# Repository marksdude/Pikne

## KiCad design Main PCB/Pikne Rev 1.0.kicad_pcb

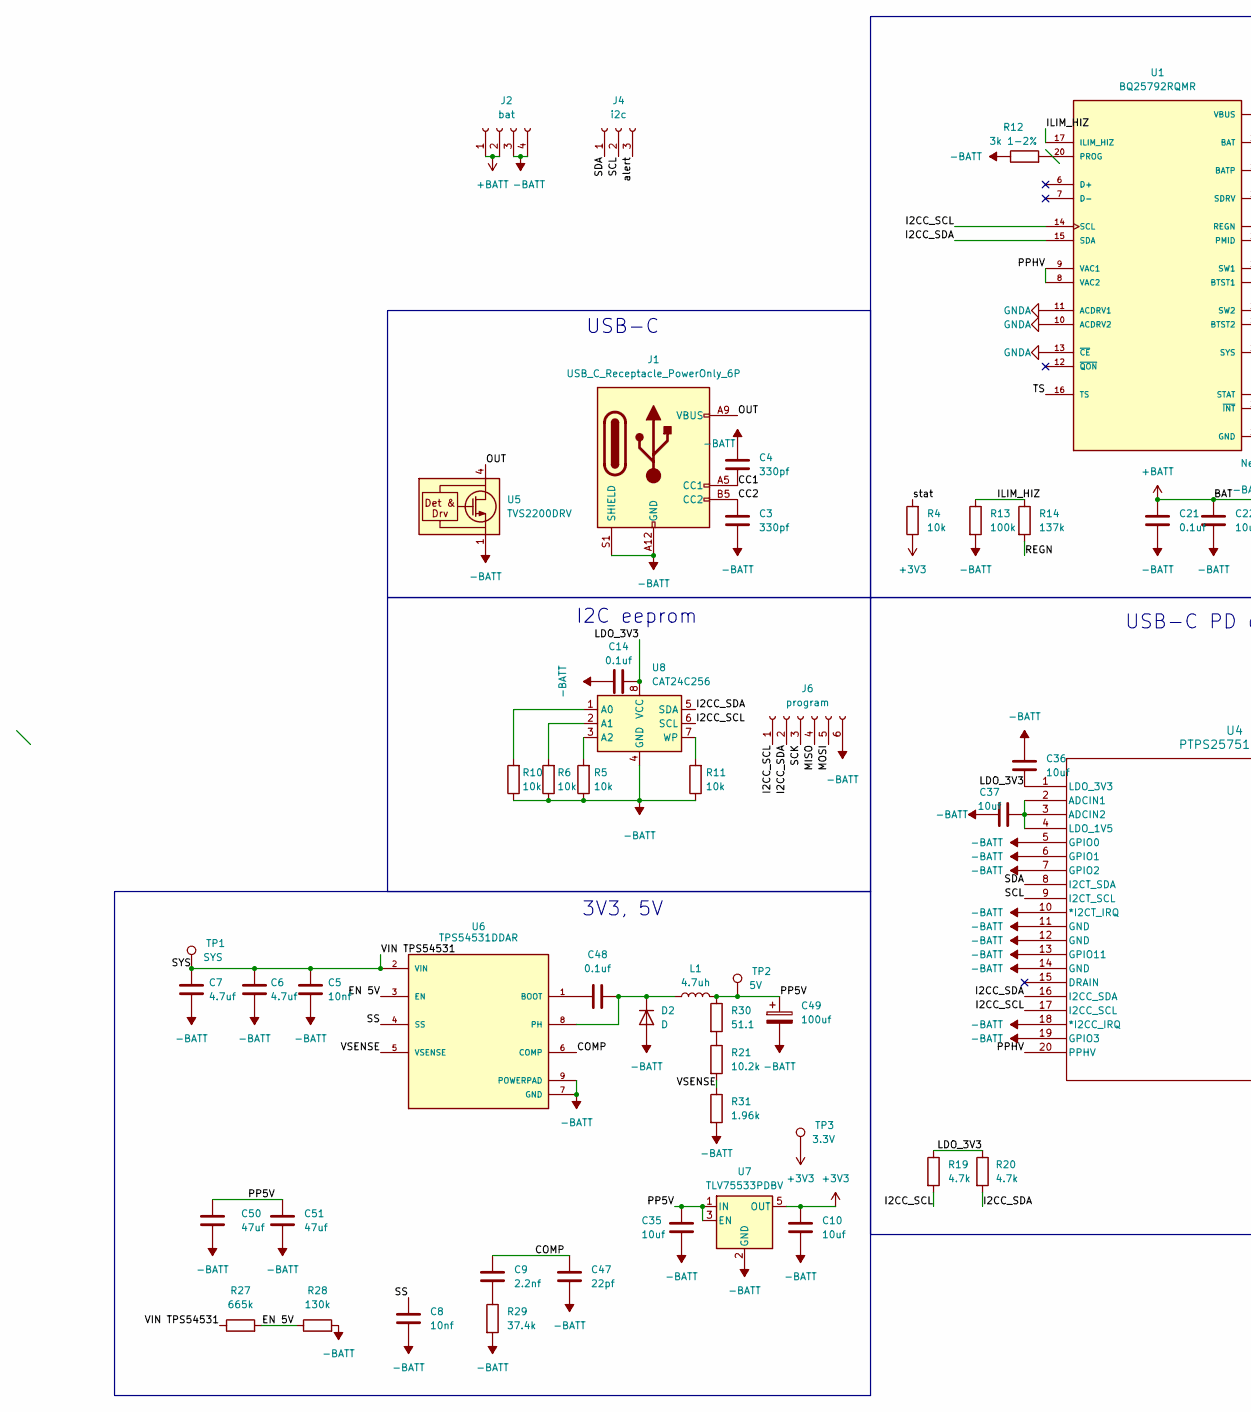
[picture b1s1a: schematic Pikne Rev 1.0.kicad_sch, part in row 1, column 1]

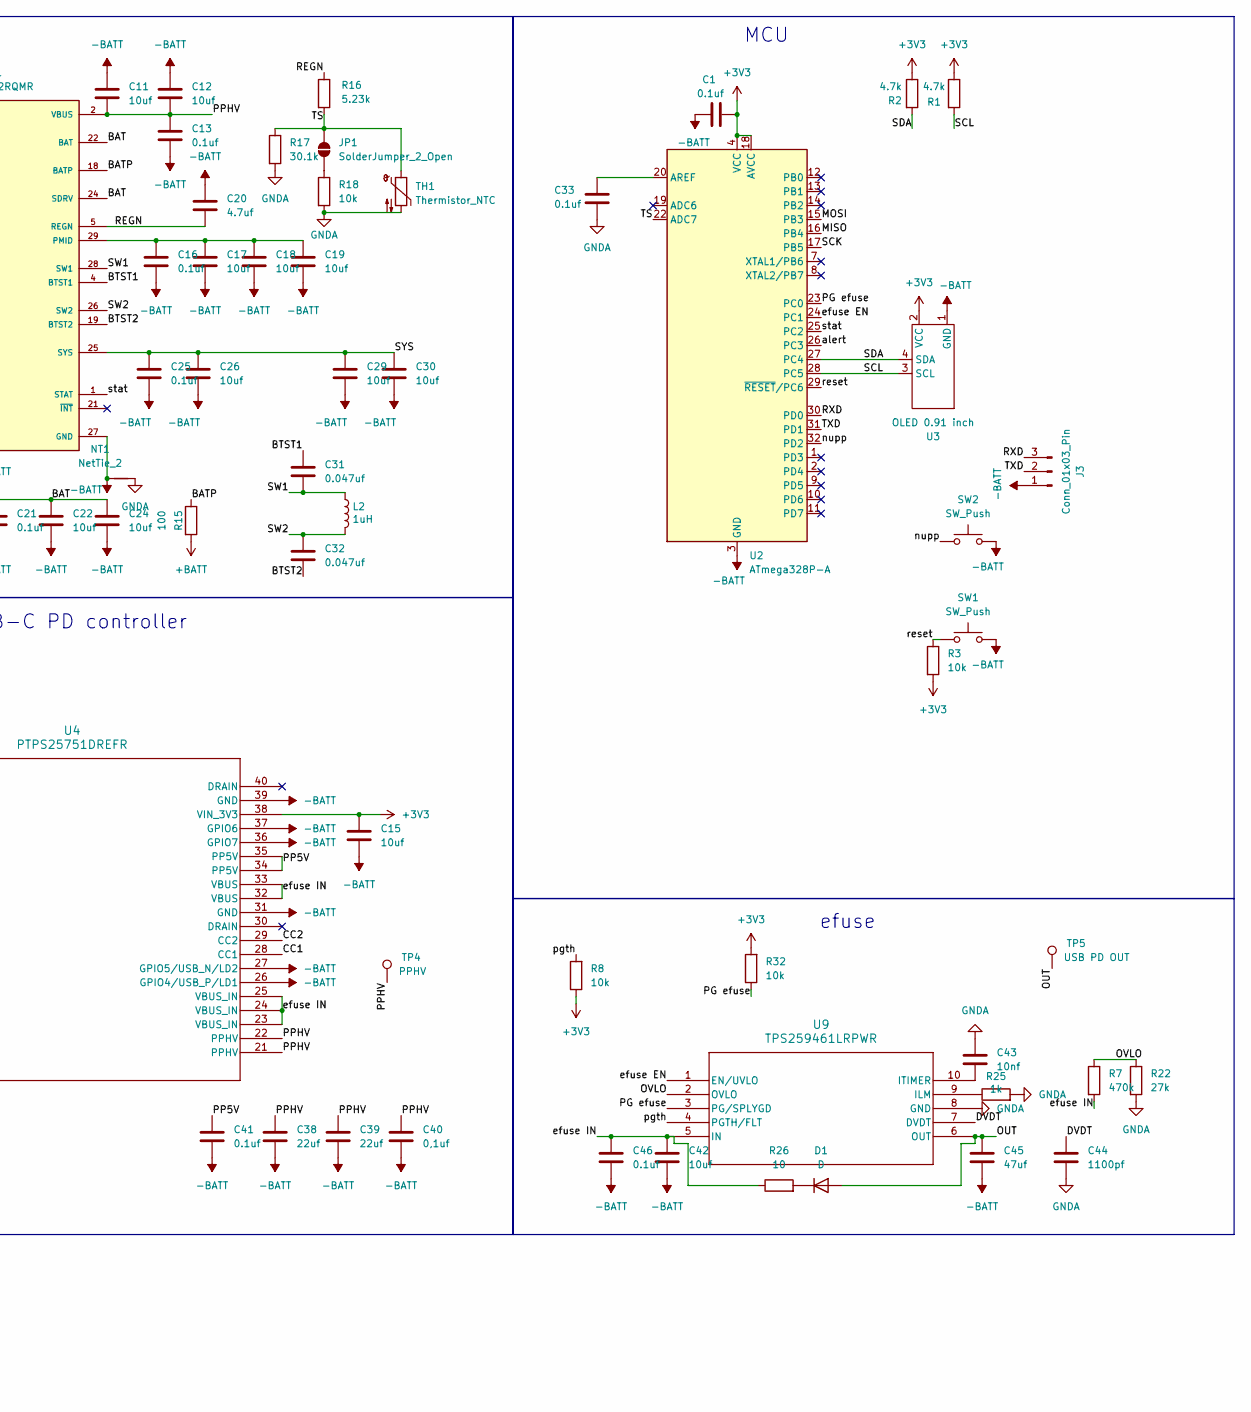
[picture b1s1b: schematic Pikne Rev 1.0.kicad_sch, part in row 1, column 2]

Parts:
C1, C13, C14, C16, C21, C25, C33, C41, C46, C48: 0.1uf; C_0201_0603Metric_Pad0.64x0.40mm_HandSolder
C3, C4: 330pf; C_0402_1005Metric_Pad0.74x0.62mm_HandSolder
C5, C8, C43: 10nf; C_0201_0603Metric_Pad0.64x0.40mm_HandSolder
C6, C7, C20: 4.7uf; C_0402_1005Metric_Pad0.74x0.62mm_HandSolder
C9: 2.2nf; C_0402_1005Metric_Pad0.74x0.62mm_HandSolder
C10, C11, C12, C22, C24, C26, C29, C30, C35: 10uf; C_0603_1608Metric_Pad1.08x0.95mm_HandSolder
C15, C36, C37: 10uf; C_0402_1005Metric_Pad0.74x0.62mm_HandSolder
C17, C18, C19, C42: 10uf; R_0603_1608Metric_Pad0.98x0.95mm_HandSolder
C31, C32: 0.047uf; C_0402_1005Metric_Pad0.74x0.62mm_HandSolder
C38, C39: 22uf; C_0805_2012Metric_Pad1.18x1.45mm_HandSolder
C40: 0,1uf; C_0201_0603Metric_Pad0.64x0.40mm_HandSolder
C44: 1100pf; C_0402_1005Metric_Pad0.74x0.62mm_HandSolder
C45, C50, C51: 47uf; C_1210_3225Metric_Pad1.33x2.70mm_HandSolder
C47: 22pf; C_0402_1005Metric_Pad0.74x0.62mm_HandSolder
C49: 100uf; CP_Radial_D5.0mm_P2.50mm
D1: D; D_SOD-323_HandSoldering
D2: D; D_SMC
J1: USB_C_Receptacle_PowerOnly_6P; USB_C_Receptacle_GCT_USB4125-xx-x-0190_6P_TopMnt_Horizontal
J2: bat; JST_VH_S4P-VH_1x04_P3.96mm_Horizontal
J3: Conn_01x03_Pin; JST_ZH_B3B-ZR_1x03_P1.50mm_Vertical
J4: i2c; JST_ZH_B3B-ZR_1x03_P1.50mm_Vertical
J6: program; JST_ZH_B6B-ZR_1x06_P1.50mm_Vertical
JP1: SolderJumper_2_Open; SolderJumper-2_P1.3mm_Open_Pad1.0x1.5mm
L1: 4.7uh; L_Bourns_SRP1038C_10.0x10.0mm
L2: 1uH; L_Vishay_IHLP-2020
NT1: NetTie_2; NetTie-2_THT_Pad0.3mm
R1, R2: 4.7k; R_0603_1608Metric_Pad0.98x0.95mm_HandSolder
R3, R18, R32: 10k; R_0603_1608Metric_Pad0.98x0.95mm_HandSolder
R4, R5, R6, R8, R10, R11: 10k; R_0402_1005Metric_Pad0.72x0.64mm_HandSolder
R7: 470k; R_0402_1005Metric_Pad0.72x0.64mm_HandSolder
R12: 3k 1-2%; R_0402_1005Metric_Pad0.72x0.64mm_HandSolder
R13: 100k; R_0603_1608Metric_Pad0.98x0.95mm_HandSolder
R14: 137k; R_0603_1608Metric_Pad0.98x0.95mm_HandSolder
R15: 100; R_0402_1005Metric_Pad0.72x0.64mm_HandSolder
R16: 5.23k; R_0603_1608Metric_Pad0.98x0.95mm_HandSolder
R17: 30.1k; R_0603_1608Metric_Pad0.98x0.95mm_HandSolder
R19, R20: 4.7k; R_0402_1005Metric_Pad0.72x0.64mm_HandSolder
R21: 10.2k; R_0603_1608Metric_Pad0.98x0.95mm_HandSolder
R22: 27k; R_0402_1005Metric_Pad0.72x0.64mm_HandSolder
R25: 1k; R_0402_1005Metric_Pad0.72x0.64mm_HandSolder
R26: 10; R_0402_1005Metric_Pad0.72x0.64mm_HandSolder
R27: 665k; R_0603_1608Metric_Pad0.98x0.95mm_HandSolder
R28: 130k; R_0603_1608Metric_Pad0.98x0.95mm_HandSolder
R29: 37.4k; R_0402_1005Metric_Pad0.72x0.64mm_HandSolder
R30: 51.1; R_0603_1608Metric_Pad0.98x0.95mm_HandSolder
R31: 1.96k; R_0603_1608Metric_Pad0.98x0.95mm_HandSolder
SW1, SW2: SW_Push; SW_SPST_B3U-1000P
TH1: Thermistor_NTC; ntc
TP1: SYS; TestPoint_Pad_D1.0mm
TP2: 5V; TestPoint_Pad_D1.0mm
TP3: 3.3V; TestPoint_Pad_D1.0mm
TP4: PPHV; TestPoint_Pad_D1.0mm
TP5: USB PD OUT; TestPoint_Pad_D1.0mm
U1: BQ25792RQMR; QFN40P400X400X100-29N; PARTREV 11/2019
U2: ATmega328P-A; TQFP-32_7x7mm_P0.8mm
U3: OLED 0.91 inch; SSD1306-0.91-OLED-4pin-128x32
U4: PTPS25751DREFR; WQFN38_REF_TEX
U5: TVS2200DRV; WSON-6-1EP_2x2mm_P0.65mm_EP1x1.6mm
U6: TPS54531DDAR; CONV_TPS54531DDAR; PARTREV A
U7: TLV75533PDBV; SOT-23-5
U8: CAT24C256; SOIC-8_3.9x4.9mm_P1.27mm
U9: TPS259461LRPWR; VQFN10_RPW_TEX

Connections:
+3V3: C1.2, C10.1, C15.1, R1.1, R2.1, R3.2, R4.1, R8.1, R32.2, TP3.1 (1_1), U2.4 (VCC), U2.6 (VCC), U2.18 (AVCC), U3.2 (VCC), U4.38 (VIN_3V3), U7.5 (OUT)
+BATT: C21.1, C22.1, C24.1, J2.1, J2.2, R15.2, U1.22 (BAT), U1.23 (BAT), U1.24 (SDRV)
-BATT: C1.1, C3.2, C4.1, C5.2, C6.2, C7.1, C8.2, C10.2, C11.1, C12.1, C13.1, C14.2, C15.2, C16.2, C17.2, C18.2, C19.2, C20.1, C21.2, C22.2, C24.2, C25.2, C26.2, C29.2, C30.2, C35.2, C36.2, C37.2, C38.2, C39.2, C40.2, C41.2, C42.2, C45.2, C46.2, C47.2, C49.2, C50.2, C51.2, D2.2 (A), J1.A12 (GND), J1.B12 (GND), J1.S1 (SHIELD), J2.3, J2.4, J3.1, J6.6, NT1.1, R5.1, R6.1, R10.1, R11.1, R12.1, R13.2, R28.2, R29.2, R31.2, SW1.2, SW2.2, U1.27 (GND), U2.3 (GND), U2.5 (GND), U2.21 (GND), U3.1 (GND), U4.5 (GPIO0), U4.6 (GPIO1), U4.7 (GPIO2), U4.10 (*I2CT_IRQ), U4.11 (GND), U4.12 (GND), U4.13 (GPIO11), U4.14 (GND), U4.18 (*I2CC_IRQ), U4.19 (GPIO3), U4.26 (GPIO4/USB_P/LD1), U4.27 (GPIO5/USB_N/LD2), U4.31 (GND), U4.36 (GPIO7), U4.37 (GPIO6), U4.39 (GND), U5.1 (GND), U5.2 (GND), U5.3 (GND), U5.7 (GND), U6.7 (GND), U6.9 (POWERPAD), U7.2 (GND), U8.4 (GND)
/BATP: R15.1, U1.18 (BATP)
/BTST1: C31.1, U1.4 (BTST1)
/BTST2: C32.2, U1.19 (BTST2)
/CC1: C4.2, J1.A5 (CC1), U4.28 (CC1)
/CC2: C3.1, J1.B5 (CC2), U4.29 (CC2)
/COMP: C9.1, C47.1, U6.6 (COMP)
/DVDT: C44.1, U9.7 (DVDT)
/EN 5V: R27.2, R28.1, U6.3 (EN)
/I2CC_SCL: J6.1, R19.2, U1.14 (SCL), U4.17 (I2CC_SCL), U8.6 (SCL)
/I2CC_SDA: J6.2, R20.2, U1.15 (SDA), U4.16 (I2CC_SDA), U8.5 (SDA)
/ILIM_HIZ: R13.1, R14.1, U1.17 (ILIM_HIZ)
/LDO_3V3: C14.1, C36.1, R19.1, R20.1, U4.1 (LDO_3V3), U8.8 (VCC)
/MISO: J6.4, U2.16 (PB4)
/MOSI: J6.5, U2.15 (PB3)
/OUT: C45.1, D1.2 (A), J1.A9 (VBUS), J1.B9 (VBUS), TP5.1 (1_1), U5.4 (IN), U5.5 (IN), U5.6 (IN), U9.6 (OUT)
/OVLO: R7.1, R22.1, U9.2 (OVLO)
/PG efuse: R32.1, U2.23 (PC0), U9.3 (PG/SPLYGD)
/PP5V: C35.1, C41.1, C49.1, C50.1, C51.1, L1.2, R30.1, TP2.1 (1_1), U4.34 (PP5V), U4.35 (PP5V), U7.1 (IN), U7.3 (EN)
/REGN: C20.2, R14.2, R16.1, U1.5 (REGN)
/RXD: J3.3, U2.30 (PD0)
/SCK: J6.3, U2.17 (PB5)
/SCL: J4.2, R1.2, U2.28 (PC5), U3.3 (SCL), U4.9 (I2CT_SCL)
/SDA: J4.1, R2.2, U2.27 (PC4), U3.4 (SDA), U4.8 (I2CT_SDA)
/SS: C8.1, U6.4 (SS)
/SW1: C31.2, L2.1, U1.28 (SW1)
/SW2: C32.1, L2.2, U1.26 (SW2)
/SYS: C5.1, C6.1, C7.2, C25.1, C26.1, C29.1, C30.1, R27.1, TP1.1 (1_1), U1.25 (SYS), U6.2 (VIN)
/TS: JP1.1 (A), R16.2, R17.1, TH1.1, U1.16 (TS), U2.22 (ADC7)
/TXD: J3.2, U2.31 (PD1)
/VSENSE: R21.2, R31.1, U6.5 (VSENSE)
/alert: J4.3, U2.26 (PC3)
/efuse EN: U2.24 (PC1), U9.1 (EN/UVLO)
/efuse IN: C42.1, C46.1, R7.2, R26.1, U4.23 (VBUS_IN), U4.24 (VBUS_IN), U4.25 (VBUS_IN), U4.32 (VBUS), U4.33 (VBUS), U9.5 (IN)
/nupp: SW2.1, U2.32 (PD2)
/pgth: R8.2, U9.4 (PGTH/FLT)
/reset: R3.1, SW1.1, U2.29 (~RESET/PC6)
/stat: R4.2, U1.1 (STAT), U2.25 (PC2)
GNDA: C33.2, C43.1, C44.2, NT1.2, R17.2, R18.2, R22.2, R25.2, TH1.2, U1.10 (ACDRV2), U1.11 (ACDRV1), U1.13 (~CE), U9.8 (GND)
unnamed: C9.2, R29.1
unnamed: D1.1 (K), R26.2
unnamed: C48.2, D2.1 (K), L1.1, U6.8 (PH)
unnamed: JP1.2 (B), R18.1
unnamed: R21.1, R30.2
unnamed: C16.1, C17.1, C18.1, C19.1, U1.29 (PMID)
unnamed: R12.2, U1.20 (PROG)
unnamed: C33.1, U2.20 (AREF)
unnamed: C37.1, U4.2 (ADCIN1), U4.3 (ADCIN2), U4.4 (LDO_1V5)
unnamed: C48.1, U6.1 (BOOT)
unnamed: R10.2, U8.1 (A0)
unnamed: R6.2, U8.2 (A1)
unnamed: R5.2, U8.3 (A2)
unnamed: R11.2, U8.7 (WP)
unnamed: R25.1, U9.9 (ILM)
unnamed: C43.2, U9.10 (ITIMER)
VBUS: C11.2, C12.2, C13.2, C38.1, C39.1, C40.1, TP4.1 (1_1), U1.2 (VBUS), U1.3 (VBUS), U1.8 (VAC2), U1.9 (VAC1), U4.20 (PPHV), U4.21 (PPHV), U4.22 (PPHV)

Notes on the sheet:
USB-C PD controller
MCU
3V3, 5V
I2C eeprom
efuse
USB-C

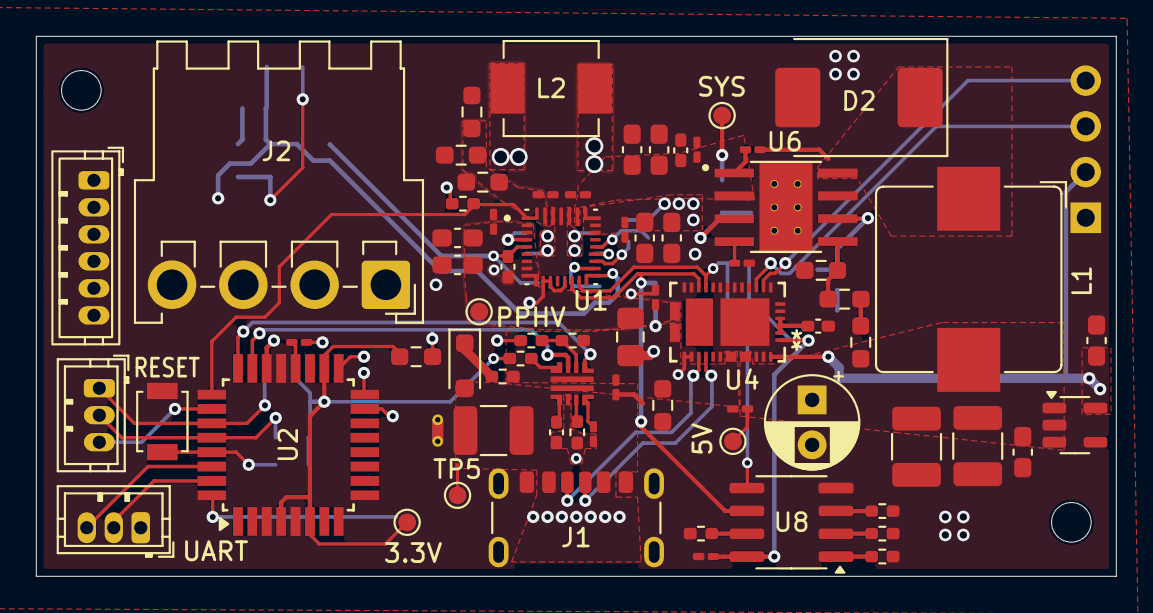
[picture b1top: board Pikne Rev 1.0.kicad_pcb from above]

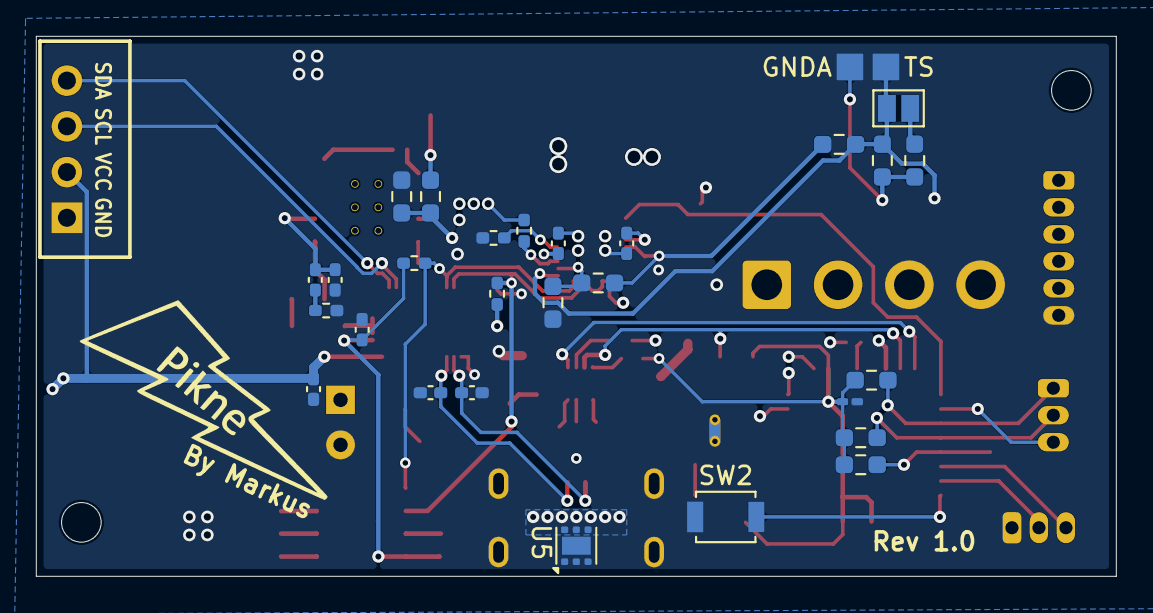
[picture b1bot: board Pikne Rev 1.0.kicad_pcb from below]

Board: 4 copper layers, 60.0 x 30.0 mm, 100 parts (29 on the bottom side), 58 nets.

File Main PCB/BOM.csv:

Id;Designator;Footprint;Quantity;Designation;Price (total) (EUR);Link;Part number
1;C1, C13, C14, C16, C21, C23, C25, C33, C41, C46, C48, C40;C_0402_1005Metric;12;0.1uf;0,18;https://www.mouser.ee/en/ProductDetail/Murata-Electronics/GR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;GRM155R62A104ME14D 
2;C2;C_0402_1005Metric;1;1nf;0,1;https://www.mouser.ee/en/ProductDetail/Walsin/0402B102M500CT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;0402B102M500CT
3;C3, C4;C_0402_1005Metric_Pad0.74x0.62mm_HandSolder;2;330pf;0,16;https://www.mouser.ee/en/ProductDetail/Samsung-Electro-Mecha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;CL05C331JB5NNNC 
4;C5, C8, C27, C43;C_0402_1005Metric;4;10nf;0,14;https://www.mouser.ee/en/ProductDetail/Murata-Electronics/GR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;GRT155R71E103KE01J 
5;C6, C20;C_0402_1005Metric;2;4.7uf;0,4;https://www.mouser.ee/en/ProductDetail/KYOCERA-AVX/KGM05CR51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;KGM05CR51C475MH 
6;C9;C_0402_1005Metric_Pad0.74x0.62mm_HandSolder;1;2.2nf;0,1;https://www.mouser.ee/en/ProductDetail/Murata-Electronics/GR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;GRM155R71H222KA01D 
7;C10, C35;C_0603_1608Metric_Pad1.08x0.95mm_HandSolder;2;10uf;0,21;https://www.mouser.ee/en/ProductDetail/Murata-Electronics/GR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;GRM188R61A106ME69D 
8;C11, C12, C42;C_0805_2012Metric;3;10uf;1,21;https://www.mouser.ee/en/ProductDetail/TDK/C2012X5R1V106K085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;C2012X5R1V106K085AC 
9;C15, C17, C18, C19, C22, C24, C26, C29, C30, C37, C36;C_0603_1608Metric;11;10uf;0,97;https://www.mouser.ee/en/ProductDetail/KYOCERA-AVX/0603YD106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;0603YD106KAT2A 
10;C31, C32;C_0402_1005Metric_Pad0.74x0.62mm_HandSolder;2;0.047uf;0,14;https://www.mouser.ee/en/ProductDetail/Murata-Electronics/GR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;GRM155R71H473ME14J 
11;;;;;;;
12;C38, C39;C_0805_2012Metric;2;22uf;1,1;https://www.mouser.ee/en/ProductDetail/TAIYO-YUDEN/MSAST21GB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;MSAST21GBB5226MTNC12
13;C40;;;;;;
14;C44;C_0402_1005Metric;1;1100pf;0,13;https://www.mouser.ee/en/ProductDetail/KEMET/C0402C112J4HACA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;C0402C112J4HACAUTO
15;C45;C_0603_1608Metric;1;4.7uf;0,27;https://www.mouser.ee/en/ProductDetail/Murata-Electronics/GR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;GRM188R6YA475ME15D
16;C47;C_0402_1005Metric_Pad0.74x0.62mm_HandSolder;1;22pf;0,11;https://www.mouser.ee/en/ProductDetail/Walsin/0402N220K500CT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;0402N220K500CT
17;C49;CP_Radial_D5.0mm_P2.50mm;1;100uf;;;
18;C50, C51;C_1210_3225Metric_Pad1.33x2.70mm_HandSolder;2;47uf;1,15;https://www.mouser.ee/en/ProductDetail/Samsung-Electro-Mecha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;CL32A476MOJNNNE
19;D1;D_SOD-323_HandSoldering;1;;0,23;https://www.mouser.ee/en/ProductDetail/Taiwan-Semiconductor/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;BAT42WSH RRG 
20;D2;D_SMC;1;;0,95;https://www.mouser.ee/en/ProductDetail/Comchip-Technology/CD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;CDBC540-G 
21;D3;LED_0603_1608Metric;1;LED blue;0,15;https://www.mouser.ee/en/ProductDetail/Wurth-Elektronik/1500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;150060BS75000 
22;J1;USB_C_Receptacle_GCT_USB4125-xx-x-0190_6P_TopMnt_Horizontal;1;USB_C_Receptacle_PowerOnly_6P;0,53;https://www.mouser.ee/ProductDetail/GCT/USB4125-GF-A?qs=KUoI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;USB4125-GF-A 
23;J2;JST_VH_S4P-VH_1x04_P3.96mm_Horizontal;1;JST VH S4P;0,26;https://www.mouser.ee/en/ProductDetail/JST-Commercial/S4P-VH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;S4P-VH(LF)(SN) 
24;J3, J4;JST_ZH_B3B-ZR_1x03_P1.50mm_Vertical;2;JST ZH B3B;0,41;https://www.mouser.ee/en/ProductDetail/JST-Commercial/B3B-ZR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;B3B-ZR-3.4(LF)(SN) 
25;;;;;;;
26;J6;JST_ZH_B6B-ZR_1x06_P1.50mm_Vertical;1;JST ZH B6B;0,28;https://www.mouser.ee/en/ProductDetail/JST-Commercial/B6B-ZR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;B6B-ZR-3.4(LF)(SN) 
27;L1;L_Bourns_SRP1038C_10.0x10.0mm;1;4.7uh;0,74;https://www.mouser.ee/en/ProductDetail/Bourns/SRP1038CC-4R7M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;SRP1038CC-4R7M 
28;L3;7443845030010;1;1uH;1,89;https://www.mouser.ee/en/ProductDetail/Wurth-Elektronik/7443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;7443845030010
29;R1, R2, R26;R_0603_1608Metric;3;4.7k;0,09;https://www.mouser.ee/en/ProductDetail/YAGEO/AC0603JR-074K7L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;AC0603JR-074K7L 
30;R3, R18, R4, R8, R9, R32;R_0603_1608Metric;6;10k;0,09;https://www.mouser.ee/en/ProductDetail/YAGEO/RT0603FRE1310KL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;RT0603FRE1310KL 
31;;;;;;;
32;R5, R6, R10, R11, R23;R_0402_1005Metric;5;10k;0,08;https://www.mouser.ee/en/ProductDetail/YAGEO/RC0402FR-0710KL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;RC0402FR-0710KL 
33;R7;R_0402_1005Metric;1;470k;0,09;https://www.mouser.ee/en/ProductDetail/YAGEO/RC0402FR-7D470K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;RC0402FR-7D470KL 
34;R12;R_0402_1005Metric;1;6.04k;0,09;https://www.mouser.ee/en/ProductDetail/YAGEO/RT0402FRE076K04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;RT0402FRE076K04L 
35;R13;R_0603_1608Metric;1;100k;0,09;https://www.mouser.ee/en/ProductDetail/YAGEO/RC0603FR-10100K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;RC0603FR-10100KL 
36;R14;R_0603_1608Metric;1;137k;0,09;https://www.mouser.ee/en/ProductDetail/YAGEO/AC0603FR-07137K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;AC0603FR-07137KL 
37;R15;R_0402_1005Metric;1;100 Ohm;0,08;https://www.mouser.ee/en/ProductDetail/YAGEO/AC0402FR-13100R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;AC0402FR-13100RL 
38;R16;R_0603_1608Metric_Pad0.98x0.95mm_HandSolder;1;5.23k;0,09;https://www.mouser.ee/en/ProductDetail/YAGEO/AC0603FR-075K23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;AC0603FR-075K23L 
39;R17;R_0603_1608Metric_Pad0.98x0.95mm_HandSolder;1;30.1k;0,1;https://www.mouser.ee/en/ProductDetail/Walsin/WR06X3012FTL?q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;WR06X3012FTL 
40;R19, R20;R_0402_1005Metric;2;4.7k;0,07;https://www.mouser.ee/en/ProductDetail/YAGEO/RC0402JR-104K7L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;RC0402JR-104K7L 
41;R21;R_0603_1608Metric;1;10.2k;0,09;https://www.mouser.ee/en/ProductDetail/YAGEO/RT0603FRE0710K2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;RT0603FRE0710K2L 
42;R22;R_0402_1005Metric;1;27k;0,09;https://www.mouser.ee/en/ProductDetail/Walsin/WR04X2702FTL?q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;WR04X2702FTL 
43;;;;;;;
44;R24;R_0603_1608Metric;1;47 Ohm;0,09;https://www.mouser.ee/en/ProductDetail/YAGEO/RT0603FRE0747RL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;RT0603FRE0747RL 
45;R25;R_0402_1005Metric;1;1k;0,09;https://www.mouser.ee/en/ProductDetail/YAGEO/RC0402FR-101KL?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;RC0402FR-101KL 
46;;;;;;;
47;R27;R_0603_1608Metric_Pad0.98x0.95mm_HandSolder;1;665k;0,09;https://www.mouser.ee/en/ProductDetail/SEI-Stackpole/RMCF060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;RMCF0603FT665K 
48;R28;R_0603_1608Metric_Pad0.98x0.95mm_HandSolder;1;130k;0,09;https://www.mouser.ee/en/ProductDetail/SEI-Stackpole/RMCF060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;RMCF0603FT130K 
49;R29;R_0402_1005Metric_Pad0.72x0.64mm_HandSolder;1;37.4k;0,08;https://www.mouser.ee/en/ProductDetail/YAGEO/RC0402FR-0737K4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;RC0402FR-0737K4L 
50;R30;R_0603_1608Metric;1;51.1;0,07;https://www.mouser.ee/en/ProductDetail/SEI-Stackpole/RMCF060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;RMCF0603FT51R1 
51;R31;R_0603_1608Metric;1;1.96k;0,09;https://www.mouser.ee/en/ProductDetail/SEI-Stackpole/RMCF060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;RMCF0603FT1K96 
52;R33;R_0603_1608Metric;1;10 Ohm;0,08;https://www.mouser.ee/en/ProductDetail/Walsin/WR06X100-JTL?q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;WR06X100 JTL 
53;SW1, SW2;SW_SPST_B3U-1000P;2;SW_Push;1,87;https://www.mouser.ee/en/ProductDetail/Omron-Electronics/B3U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;B3U-1000P 
54;TH1;ntc;1;NTC 10K;0,58;https://www.mouser.ee/en/ProductDetail/Semitec/103AT-2?qs=wg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;103AT-2 
55;TP1;TestPoint_Pad_D1.0mm;1;;;;
56;TP2;TestPoint_Pad_D1.0mm;1;;;;
57;TP3;TestPoint_Pad_D1.0mm;1;;;;
58;TP4;TestPoint_Pad_D1.0mm;1;;;;
59;TP5;TestPoint_Pad_D1.0mm;1;;;;
60;U1;QFN40P400X400X100-29N;1;BQ25792RQMR;6,33;https://www.mouser.ee/en/ProductDetail/Texas-Instruments/BQ2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;BQ25792RQMR 
61;U2;TQFP-32_7x7mm_P0.8mm;1;ATmega328P-A;2,29;https://www.mouser.ee/en/ProductDetail/Microchip-Technology/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;ATMEGA328P-AU 
62;U3;SSD1306-0.91-OLED-4pin-128x32;1;OLED 0.91 inch;2,64;https://www.aliexpress.com/item/1005008640108394.html;
63;U4;WQFN38_REF_TEX;1;TPS25751DREFR;2,57;https://www.mouser.ee/en/ProductDetail/Texas-Instruments/TPS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;TPS25751DREFR 
64;U5;WSON-6-1EP_2x2mm_P0.65mm_EP1x1.6mm;1;TVS2200DRV;0,93;https://www.mouser.ee/en/ProductDetail/Texas-Instruments/TVS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;TVS2200DRVR 
65;U6;CONV_TPS54531DDAR;1;TPS54531DDAR;1,95;https://www.mouser.ee/en/ProductDetail/Texas-Instruments/TPS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;TPS54531DDAR 
66;U7;SOT-23-5;1;TLV75533PDBV;0,38;https://www.mouser.ee/en/ProductDetail/Texas-Instruments/TLV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;TLV75533PDBVR 
67;U8;SOIC-8_3.9x4.9mm_P1.27mm;1;CAT24C256;0,63;https://www.mouser.ee/en/ProductDetail/onsemi/CAT24C256WI-GT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;CAT24C256WI-GT3 
68;U9;VQFN10_RPW_TEX;1;TPS259461ARPW;1,27;https://www.mouser.ee/en/ProductDetail/Texas-Instruments/TPS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;TPS259461ARPWR 
;;;;Total (EUR);35,07;;
;;;;Total (USD);40,69;;

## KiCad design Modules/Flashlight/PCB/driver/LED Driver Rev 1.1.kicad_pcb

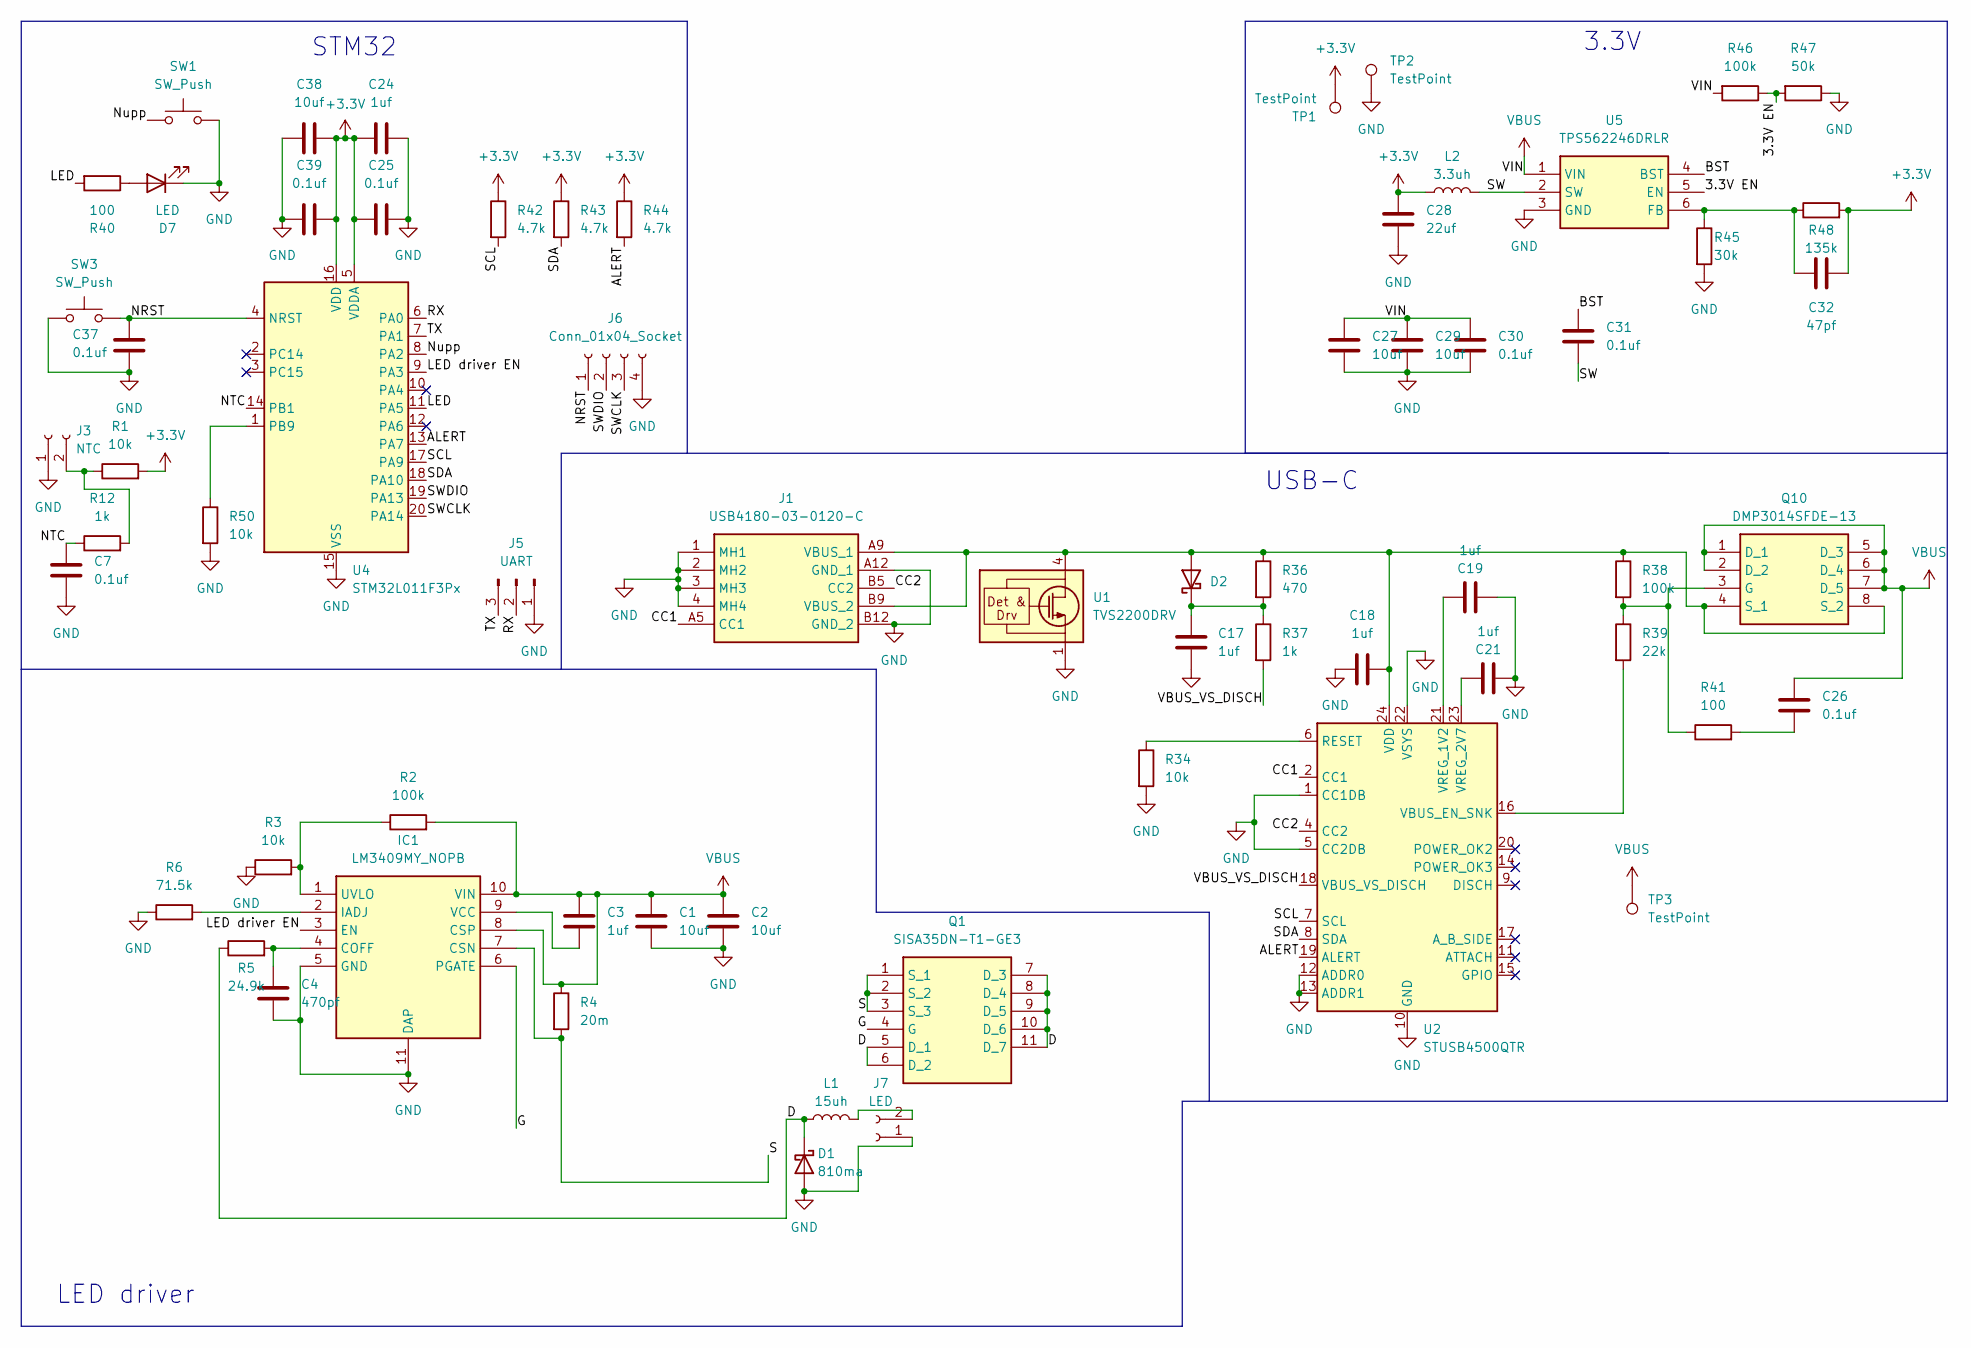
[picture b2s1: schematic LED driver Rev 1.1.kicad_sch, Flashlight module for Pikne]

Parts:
C1, C2: 10uf; C_1206_3216Metric
C3, C19, C21: 1uf; C_0402_1005Metric
C4: 470pf; C_0402_1005Metric
C7, C25, C26, C30, C31, C37, C39: 0.1uf; C_0402_1005Metric
C17, C18, C24: 1uf; C_0603_1608Metric
C27, C29, C38: 10uf; C_0603_1608Metric
C28: 22uf; C_0805_2012Metric
C32: 47pf; R_0402_1005Metric
D1: 810ma; D_SMF
D2: D_Schottky; D_SOD-323_HandSoldering
D7: LED; LED_0603_1608Metric
IC1: LM3409MY_NOPB; SOP50P490X109-11N; Mouser Part Number 926-LM3409MY/NOPB
J1: USB4180-03-0120-C; USB4180030120C; Mouser Part Number 640-USB4180-03-0120C
J3: NTC; JST_ZH_B2B-ZR_1x02_P1.50mm_Vertical
J5: UART; JST_ZH_B3B-ZR_1x03_P1.50mm_Vertical
J6: Conn_01x04_Socket; JST_ZH_B4B-ZR_1x04_P1.50mm_Vertical
J7: LED; JST_XH_S2B-XH-A-1_1x02_P2.50mm_Horizontal
L1: 15uh; L_Bourns_SRP1038C_10.0x10.0mm
L2: 3.3uh; INDC3225X120N
Q1: SISA35DN-T1-GE3; SISA35DNT1GE3; Mouser Part Number 78-SISA35DN-T1-GE3
Q10: DMP3014SFDE-13; DMP1022UFDEQ7; Manufacturer_Part_Number DMP3014SFDE-13
R1, R3, R34: 10k; R_0603_1608Metric
R2, R38: 100k; R_0603_1608Metric
R4: 20m; R_1206_3216Metric
R5: 24.9k; R_0603_1608Metric
R6: 71.5k; R_0603_1608Metric
R12: 1k; R_0402_1005Metric
R36: 470; R_0603_1608Metric
R37: 1k; R_0603_1608Metric
R39: 22k; R_0603_1608Metric
R40, R41: 100; R_0402_1005Metric
R42, R43, R44: 4.7k; R_0603_1608Metric
R45: 30k; R_0402_1005Metric
R46: 100k; R_0402_1005Metric
R47: 50k; R_0402_1005Metric
R48: 135k; R_0402_1005Metric
R50: 10k; R_0402_1005Metric
SW1: SW_Push; SW_Tactile_SPST_Angled_PTS645Vx39-2LFS
SW3: SW_Push; SW_SPST_B3U-1000P
TP1, TP2, TP3: TestPoint; TestPoint_Pad_D1.0mm
U1: TVS2200DRV; WSON-6-1EP_2x2mm_P0.65mm_EP1x1.6mm
U2: STUSB4500QTR; QFN-24-1EP_4x4mm_P0.5mm_EP2.7x2.7mm
U4: STM32L011F3Px; TSSOP-20_4.4x6.5mm_P0.65mm
U5: TPS562246DRLR; SOTFL50P160X60-6N; Mouser Part Number 595-TPS562246DRLR

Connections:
+3.3V: C24.1, C25.1, C28.1, C32.1, C38.2, C39.2, L2.1, R1.2, R42.1, R43.1, R44.1, R48.2, TP1.1 (1_1), U4.5 (VDDA), U4.16 (VDD)
/3.3V EN: R46.1, R47.2, U5.5 (EN)
/ALERT: R44.2, U2.19 (ALERT), U4.13 (PA7)
/BST: C31.2, U5.4 (BST)
/CC1: J1.A5 (CC1), U2.2 (CC1)
/CC2: J1.B5 (CC2), U2.4 (CC2)
/D: D1.1 (K), L1.1, Q1.5 (D_1), Q1.6 (D_2), Q1.7 (D_3), Q1.8 (D_4), Q1.9 (D_5), Q1.10 (D_6), Q1.11 (D_7), R5.1
/G: IC1.6 (PGATE), Q1.4 (G)
/LED: R40.2, U4.11 (PA5)
/LED driver EN: IC1.3 (EN), U4.9 (PA3)
/NRST: C37.2, J6.1, SW3.2, U4.4 (NRST)
/NTC: C7.1, R12.1, U4.14 (PB1)
/Nupp: SW1.1, U4.8 (PA2)
/RX: J5.2, U4.6 (PA0)
/S: IC1.7 (CSN), Q1.1 (S_1), Q1.2 (S_2), Q1.3 (S_3), R4.2
/SCL: R42.2, U2.7 (SCL), U4.17 (PA9)
/SDA: R43.2, U2.8 (SDA), U4.18 (PA10)
/SW: C31.1, L2.2, U5.2 (SW)
/SWCLK: J6.3, U4.20 (PA14)
/SWDIO: J6.2, U4.19 (PA13)
/TX: J5.3, U4.7 (PA1)
/VBUS_VS_DISCH: R37.2, U2.18 (VBUS_VS_DISCH)
GND: C1.2, C2.2, C4.2, C7.2, C17.1, C18.1, C19.1, C21.1, C24.2, C25.2, C27.2, C28.2, C29.2, C30.2, C37.1, C38.1, C39.1, D1.2 (A), D7.1 (K), IC1.5 (GND), IC1.11 (DAP), J1.1 (MH1), J1.2 (MH2), J1.3 (MH3), J1.4 (MH4), J1.A12 (GND_1), J1.B12 (GND_2), J3.1, J5.1, J6.4, J7.1, R3.1, R6.1, R34.2, R45.2, R47.1, R50.2, SW1.2, SW3.1, TP2.1 (1_1), U1.1 (GND), U1.2 (GND), U1.3 (GND), U1.7 (GND), U2.1 (CC1DB), U2.5 (CC2DB), U2.10 (GND), U2.12 (ADDR0), U2.13 (ADDR1), U2.22 (VSYS), U2.25 (GND), U4.15 (VSS), U5.3 (GND)
unnamed: C26.2, R41.2
unnamed: C18.2, D2.2 (A), J1.A9 (VBUS_1), J1.B9 (VBUS_2), Q10.4 (S_1), Q10.8 (S_2), R36.1, R38.1, U1.4 (IN), U1.5 (IN), U1.6 (IN), U2.24 (VDD)
unnamed: C17.2, D2.1 (K), R36.2, R37.1
unnamed: D7.2 (A), R40.1
unnamed: C4.1, IC1.4 (COFF), R5.2
unnamed: IC1.2 (IADJ), R6.2
unnamed: IC1.1 (UVLO), R2.1, R3.2
unnamed: C3.2, IC1.9 (VCC)
unnamed: J3.2, R1.1, R12.2
unnamed: J7.2, L1.2
unnamed: Q10.3 (G), R38.2, R39.1, R41.1
unnamed: R34.1, U2.6 (RESET)
unnamed: R39.2, U2.16 (VBUS_EN_SNK)
unnamed: C19.2, U2.21 (VREG_1V2)
unnamed: C21.2, U2.23 (VREG_2V7)
unnamed: R50.1, U4.1 (PB9)
unnamed: C32.2, R45.1, R48.1, U5.6 (FB)
VBUS: C1.1, C2.1, C3.1, C26.1, C27.1, C29.1, C30.1, IC1.8 (CSP), IC1.10 (VIN), Q10.1 (D_1), Q10.2 (D_2), Q10.5 (D_3), Q10.6 (D_4), Q10.7 (D_5), R2.2, R4.1, R46.2, TP3.1 (1_1), U5.1 (VIN)

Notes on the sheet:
3.3V
LED driver
USB-C
STM32

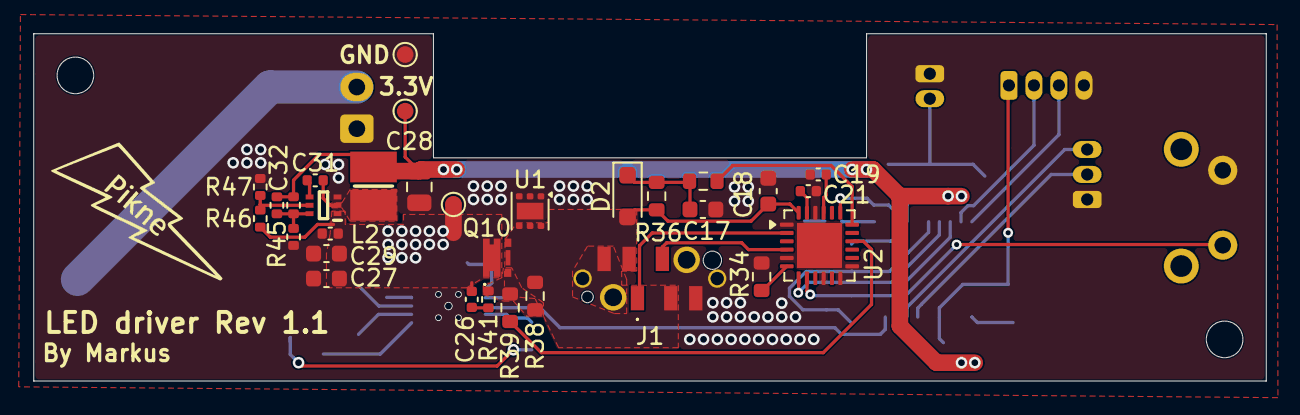
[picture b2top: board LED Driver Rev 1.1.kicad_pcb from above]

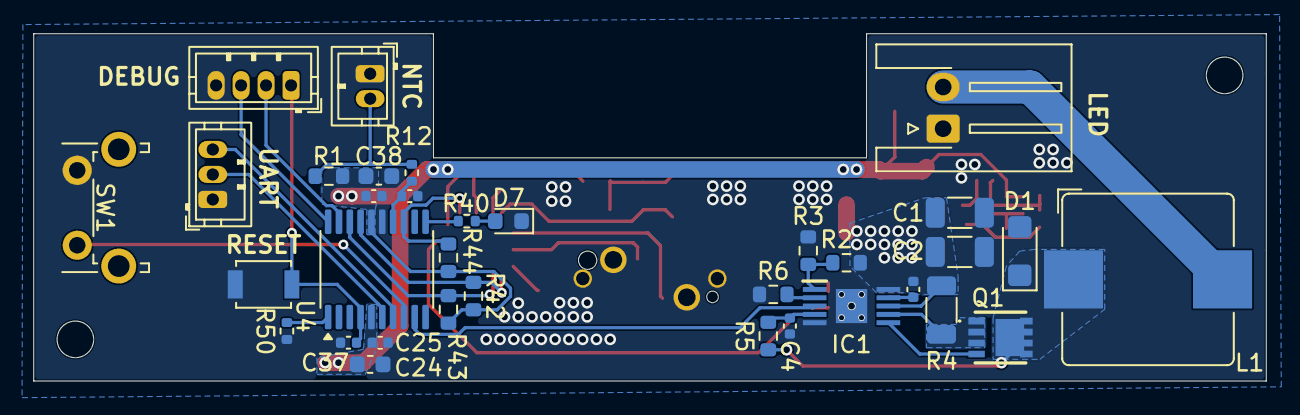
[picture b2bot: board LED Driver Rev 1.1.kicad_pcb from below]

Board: 2 copper layers, 74.0 x 20.8 mm, 65 parts (34 on the bottom side), 41 nets.

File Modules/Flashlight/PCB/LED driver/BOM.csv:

Id;Designator;Footprint;Quantity;Designation;Price (total) (EUR);Link;Part number;alternative
1;C1, C2, C27, C29;C_1206_3216Metric;4;10uf;1;https://www.mouser.ee/en/ProductDetail/TAIYO-YUDEN/MSAST31LS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;MSAST31LSB5106KTNA01 ;
2;C3, C19, C21;C_0402_1005Metric;3;1uf;0,26;https://www.mouser.ee/en/ProductDetail/Murata-Electronics/GR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;GRM155R61E105MA12D ;
3;C4;C_0402_1005Metric;1;470pf;0,09;https://www.mouser.ee/en/ProductDetail/Murata-Electronics/GC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;GCM155L81H471KA37D ;
4;C5;C_0603_1608Metric;1;4.7uf;0,27;https://www.mouser.ee/en/ProductDetail/Murata-Electronics/GR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;GRM188R6YA475ME15D ;
5;C7, C25, C26, C30, C31, C37, C39;C_0402_1005Metric;7;0.1uf;0,15;https://www.mouser.ee/en/ProductDetail/Murata-Electronics/GR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;GRM155R62A104ME14D ;
6;C17, C18, C24;C_0603_1608Metric;3;1uf;0,19;https://www.mouser.ee/en/ProductDetail/Samsung-Electro-Mecha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;CL10A105KA8NNND ;
7;C38;C_0603_1608Metric;1;10uf;0,09;https://www.mouser.ee/en/ProductDetail/Samsung-Electro-Mecha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;CL10A105KA8NFNC ;
8;C28;C_0805_2012Metric;1;22uf;0,15;https://www.mouser.ee/en/ProductDetail/Samsung-Electro-Mecha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;CL21A226MQQNNNE ;
9;C32;R_0402_1005Metric;1;47pf;0,09;https://www.mouser.ee/en/ProductDetail/Murata-Electronics/GR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;GRM1555C1H470GA01D ;
10;D1;D_SMF;1;1.2A;0,4;https://www.mouser.ee/en/ProductDetail/Vishay-Semiconductors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;V3FL45-M3/H ;
11;D2;D_SOD-323_HandSoldering;1;D_Schottky;0,13;https://www.mouser.ee/en/ProductDetail/onsemi/NSR0530HT1G?qs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;NSR0530HT1G ;
12;D3;SOT-323_SC-70;1;ESDA25W;0,36;https://www.mouser.ee/en/ProductDetail/STMicroelectronics/ES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;ESDA25W ;
13;D7;LED_0603_1608Metric;1;LED;0,28;https://www.mouser.ee/en/ProductDetail/ams-OSRAM/KT-EELP41.1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;KT EELP41.12-S2U1-25-2X4X-5-R18 ;
14;IC1;SOP50P490X109-11N;1;LM3409MY_NOPB;2,41;https://www.mouser.ee/en/ProductDetail/Texas-Instruments/LM3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;LM3409HVMYX/NOPB ;
15;J1;USB4180030120C;1;USB4180-03-0120-C;0,87;https://www.mouser.ee/en/ProductDetail/GCT/USB4180-03-0120-C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;USB4180-03-0120-C ;
16;J3;JST_ZH_B2B-ZR_1x02_P1.50mm_Vertical;1;NTC;0,1;https://www.mouser.ee/en/ProductDetail/JST-Commercial/B2B-ZR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;B2B-ZR(LF)(SN) ;
17;J5;JST_ZH_B3B-ZR_1x03_P1.50mm_Vertical;1;UART;0,21;https://www.mouser.ee/en/ProductDetail/JST-Commercial/B3B-ZR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;B3B-ZR-3.4(LF)(SN) ;
18;J6;JST_ZH_B4B-ZR_1x04_P1.50mm_Vertical;1;Conn_01x04_Socket;0,21;https://www.mouser.ee/en/ProductDetail/JST-Commercial/B4B-ZR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;B4B-ZR-3.4(LF)(SN) ;
19;J7;JST_XH_S2B-XH-A-1_1x02_P2.50mm_Horizontal;1;LED;0,13;https://www.mouser.ee/en/ProductDetail/JST-Commercial/S2B-XH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;S2B-XH-A-1(LF)(SN) ;
20;L1;L_Bourns_SRP1038C_10.0x10.0mm;1;15uh;0,84;https://www.mouser.ee/en/ProductDetail/Bourns/SRP1038CC-150M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;SRP1038CC-150M ;SRP1038C-150M 
21;L2;INDC3225X120N;1;3.3uh;0,34;https://www.mouser.ee/en/ProductDetail/Bourns/SRP3212A-3R3M?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;SRP3212A-3R3M ;
22;Q1;SISA35DNT1GE3;1;SISA35DN-T1-GE3;0,67;https://www.mouser.ee/en/ProductDetail/Vishay-Semiconductors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;SISA35DN-T1-GE3 ;
23;Q10;DMP1022UFDEQ7;1;DMP3014SFDE-13;0,43;https://www.mouser.ee/en/ProductDetail/Diodes-Incorporated/D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;DMP3014SFDE-13 ;
24;R1, R3;R_0603_1608Metric;2;10k;0,09;https://www.mouser.ee/en/ProductDetail/YAGEO/RT0603FRE1310KL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;RT0603FRE1310KL ;
25;R2, R38;R_0603_1608Metric;2;100k;0,12;https://www.mouser.ee/en/ProductDetail/YAGEO/RC0603FR-10100K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;RC0603FR-10100KL ;
26;R4;R_1206_3216Metric;1;20m;0,32;https://www.mouser.ee/en/ProductDetail/Eaton-Electronics/MFS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;MFSA1206R0200FCM ;
27;R5;R_0603_1608Metric;1;24.9k;0,09;https://www.mouser.ee/en/ProductDetail/SEI-Stackpole/RNCP060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;RNCP0603FTD24K9 ;
28;R6;R_0603_1608Metric;1;71.5k;0,09;https://www.mouser.ee/en/ProductDetail/Vishay/CRCW060371K5FK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;CRCW060371K5FKEA ;
29;R7, R9, R46;R_0402_1005Metric;3;100k;0,09;https://www.mouser.ee/en/ProductDetail/YAGEO/RC0402FR-07100K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;RC0402FR-07100KL ;
30;R12;R_0402_1005Metric;1;1k;0,09;https://www.mouser.ee/en/ProductDetail/YAGEO/RC0402FR-101KL?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;RC0402FR-101KL ;
31;R34, R50;R_0402_1005Metric;2;10k;0,09;https://www.mouser.ee/en/ProductDetail/YAGEO/RC0402FR-0710KL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;RC0402FR-0710KL ;
32;R36;R_0603_1608Metric;1;470;0,09;https://www.mouser.ee/en/ProductDetail/YAGEO/RC0603JR-07470R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;RC0603JR-07470RL ;
33;R37;R_0603_1608Metric;1;1k;0,09;https://www.mouser.ee/en/ProductDetail/YAGEO/AC0603JR-131KL?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;AC0603JR-131KL ;
34;R39;R_0603_1608Metric;1;22k;0,09;https://www.mouser.ee/en/ProductDetail/Walsin/WR06X223-JTL?q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;WR06X223 JTL ;
35;R41;R_0402_1005Metric;1;100;0,08;https://www.mouser.ee/en/ProductDetail/YAGEO/AC0402FR-13100R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;AC0402FR-13100RL ;
36;R42, R43, R44;R_0603_1608Metric;3;4.7k;0,09;https://www.mouser.ee/en/ProductDetail/YAGEO/AC0603JR-074K7L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;AC0603JR-074K7L ;
37;R45;R_0402_1005Metric;1;30k;0,08;https://www.mouser.ee/en/ProductDetail/Walsin/WR04X3002FTL?q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;WR04X3002FTL ;
38;R47;R_0402_1005Metric;1;50k;0,09;https://www.mouser.ee/en/ProductDetail/SEI-Stackpole/RNCF040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;RNCF0402DKE50K0 ;
39;R48;R_0402_1005Metric;1;135k;0,15;https://www.mouser.ee/en/ProductDetail/KOA-Speer/RN73H1ETTP1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;RN73H1ETTP1353F50 ;
40;SW1;SW_Tactile_SPST_Angled_PTS645Vx39-2LFS;1;SW_Push;0,3;https://www.mouser.ee/en/ProductDetail/CK/PTS645VM39-2-LFS?q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;PTS645VM39-2 LFS ;
41;SW3;SW_SPST_B3U-1000P;1;SW_Push;0,94;https://www.mouser.ee/en/ProductDetail/Omron-Electronics/B3U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;B3U-1000P ;
42;TP1, TP2, TP3;TestPoint_Pad_D1.0mm;3;TestPoint;;;;
43;U1;WSON-6-1EP_2x2mm_P0.65mm_EP1x1.6mm;1;TVS2200DRV;0,93;https://www.mouser.ee/en/ProductDetail/Texas-Instruments/TVS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;TVS2200DRVR ;
44;U2;QFN-24-1EP_4x4mm_P0.5mm_EP2.7x2.7mm;1;STUSB4500QTR;0,91;https://www.mouser.ee/en/ProductDetail/STMicroelectronics/ST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;STUSB4500QTR ;
45;U4;TSSOP-20_4.4x6.5mm_P0.65mm;1;STM32L011F3Px;1,58;https://www.mouser.ee/en/ProductDetail/STMicroelectronics/ST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;STM32L011F3P6 ;
46;U5;SOTFL50P160X60-6N;1;TPS562246DRLR;0,27;https://www.mouser.ee/en/ProductDetail/Texas-Instruments/TPS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;TPS562246DRLR ;
47;R40;R_0402_1005Metric;1;160;0,07;https://www.mouser.ee/en/ProductDetail/YAGEO/RC0402JR-07160R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;RC0402JR-07160RL ;
;;;;Total (EUR);16,41;;;
;;;;Total (USD);19,04;;;
